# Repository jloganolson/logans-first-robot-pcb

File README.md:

# Logan's first robot PCB

A power distribution and USB board for a two-wheeled robot with a Jetson AGX
Thor, Dynamixel servos and two 8S battery packs. It is my first real board,
it was designed with heavy help from AI coding agents, and **it has not been
built yet**. I'm publishing it to get it reviewed before I spend money on it.

> **Status (10 November 2026): not ordered.** The current revision is
> **v0.11**: 228 × 155 mm, every plug on a board edge, fully labelled. An
> unpaid JLCPCB quote exists at $321.20 for five boards with two assembled,
> but it was made from a build in which a review found a copper fault (a
> 0.37 mm neck feeding the XL330 plugs). The files here hold the corrected
> build, which has not been uploaded, quoted or independently reviewed (see
> [Open questions](#open-questions)). Nothing here has been measured on hardware.

v0.10 had an empty quarter and plugs in the middle of the board. v0.11
re-floorplans the hobby-servo block and moves the plugs to the edges:

## What it does

| Function | Detail |
|---|---|
| Battery input | Two 8S packs (27–33.6 V), each fused at the pack, through an external mechanical DPST master switch |
| Motor output | Fused battery-voltage passthrough to existing motor controllers (about 10 A in my use) |
| Jetson Thor | 24.3 V at up to 8 A, LM5146 synchronous buck, Micro-Fit plug on the left edge |
| Servo rails | 5 V (XL330), 10.8 V (XL430) and a separate 5 V (three MG90S), each a TPS54560 buck |
| Spare outputs | 5 V / 5 A and 11.7 V / 5 A on XT30 connectors |
| Audio | CM108B USB codec and TPA3118 stereo amplifier |
| USB | One USB-C to the Jetson; CH334F hub to audio, a CH342F dual UART for Dynamixel, and an STM32F072 that generates three servo PWM signals |

Four layers, 228 × 155 mm, 1 oz outer / 0.5 oz inner copper. 366 footprints, of which 304 are fitted by the factory.

## Look at it without installing anything

- **[Plain-language walkthrough](https://jloganolson.github.io/logans-first-robot-pcb/)**: what plugs in where, what it costs, what the risks are
- **[Schematic (PDF)](renders/schematic.pdf)**. See the caveat about its style below.
- [Silkscreen labels and pads](renders/board-labels.png)
- Copper layers: [top](renders/top-copper.png), [inner 1, ground](renders/inner1-ground.png), [inner 2, power](renders/inner2-power.png), [bottom](renders/bottom-copper.png), and the [assembly drawing](renders/assembly-top.png)
- Open the real board in your browser with KiCanvas: [board](https://kicanvas.org/?github=https://github.com/jloganolson/logans-first-robot-pcb/blob/main/revisions/v0.11/kicad/robot_pdb.kicad_pcb), [schematic](https://kicanvas.org/?github=https://github.com/jloganolson/logans-first-robot-pcb/blob/main/revisions/v0.11/kicad/robot_pdb.kicad_sch). The board file is about 6 MB, so it may be slow.
- KiCad 7 project: [`revisions/v0.11/kicad/`](revisions/v0.11/kicad/)

## Open questions

These are what I most want a second opinion on. Short answers are welcome;
"that's fine, everyone does it" is as useful to me as "don't".

1. **Inductor voltage ratings.** A reviewer pointed out that the molded
   inductors first chosen (Sunlord MWSA1004S, and a Cjiang part on the Thor
   rail) are rated 30 V across the winding while the packs reach 33.6 V. At
   start-up, or into a shorted output, the full input voltage sits across a
   buck inductor for each on-time. v0.11 therefore uses a 60 V Coilcraft
   XAL1510-103 on the Thor rail and 75 V Vishay IHLP-4040DZ-01 parts on the
   six TPS54560 rails, on the existing pads (about $30 in total). Was that
   necessary, or does the rating only matter in steady state? Is fitting an
   IHLP-4040 on a land pattern drawn for the Sunlord part acceptable
   (Vishay's recommended land lies inside the existing pads)?
2. **Thor buck current limit.** LM5146 with low-side RDS(on) sensing,
   R13 = 220 Ω, BSC034N06NS FETs. I calculate a typical valley limit near
   14 A (scaled from about 12 A at the earlier 180 Ω), a worst-case low near 8.5 A of load, and a worst-case inductor peak
   near 26 A (that figure was worked out against the v0.10 inductor's 29 A typical saturation; v0.11's Coilcraft XAL1510-103 is the part the design originally used). Two reviewers read the
   comparator offset's sign differently. See the [review handoff](docs/HANDOFF_V10_VALUE_ENGINEERED.md).
3. **USB 2.0 High-Speed pair.** 0.275 mm traces with a 0.19 mm gap over
   0.21 mm of 7628 prepreg (JLCPCB's calculator gives 90 Ω at 0.269 / 0.175).
   No impedance test coupon. Two older Full-Speed routes have
   [known reference-plane compromises](docs/V09_USB_PROTOTYPE_REVIEW.md).
4. **Heat.** A simple model from the real copper puts the hottest regulator
   about 45 °C above ambient at typical loads in still air, and about 78 °C
   with every output at its rated current ([map](renders/thermal-map.png),
   [model](red-team-findings/2026-11-10/thermal/)). Sensible for a board that
   will sit in a vented enclosure, or a sign the 1 oz / 0.5 oz copper is too thin?
5. **Assembly process.** JLCPCB's Economic line reflows at a fixed
   255 ± 5 °C. A reviewer reports a 250 °C case limit for the nine 10 × 10 mm
   electrolytic capacitors. Also: lead-free HASL under a 1.5 × 2 mm UQFN-10.
6. **The v0.11 changes.** The bottom strip (servo 5 V buck in the
   bottom-left corner, its fuse, the output buffer, the STM32) was re-placed
   by script, and fifteen signal links were auto-routed. The Thor plug moved
   to the left edge on a new 45 mm copper strip (In2 and bottom layer in
   parallel, about 2 mΩ by hand estimate), and the four Dynamixel plugs moved
   to the bottom edge (10.8 V on about 78 mm of In2, about 6.5 mΩ). It passes
   DRC, but nobody has reviewed the final build. Details in the
   [v0.11 handoff](docs/HANDOFF_V11_COMPACT_LAYOUT.md).
7. **Anything alarming** in the input protection (ideal-diode controller,
   TVS, fusing) or anywhere else.

## How to give feedback

Open an [issue](https://github.com/jloganolson/logans-first-robot-pcb/issues).
One issue per concern is easiest. Screenshots and "look at this net" pointers
are plenty; you don't need to propose a fix.

## How this was made, and what that means for you

- **AI-assisted and script-generated.** The schematic and layout were produced
  by Python scripts driving KiCad, written by AI agents under my direction.
  The scripts are in [`source/`](source/). Many of the older ones refer to
  earlier revisions that are not in this repository and will not run as-is.
- **The schematic is not a conventional drawing.** It is generated from a
  parts list: components are grouped by function and connected by net labels,
  with no drawn wires. It is electrically complete and matches the board, but
  it is harder to read than a hand-drawn schematic. Sorry.
- **v0.10 is a cost-reduced copy of v0.9.** A script
  ([`build_v10.py`](source/generator/build_v10.py)) takes the earlier, more
  expensive v0.9 board and applies a fixed list of changes: thinner copper,
  a shorter outline, standard via sizes, wider USB traces for the standard
  stack-up, and four part substitutions. Every change is recorded in
  [`derivation.json`](revisions/v0.10/derivation.json).
- **v0.11 is v0.10 with one area laid out again.** A second script
  ([`build_v11.py`](source/generator/build_v11.py)) moves each sub-circuit of
  the hobby-servo block as a rigid piece with its own copper, rebuilds the
  connections between them (planes for power, a grid maze router for
  signals), moves the Thor and Dynamixel plugs to the board edges, re-labels
  the silkscreen ([`labels_v11.py`](source/generator/labels_v11.py)) and
  trims the outline. The regulators, USB and audio circuitry did not move. Record: [`derivation.json`](revisions/v0.11/derivation.json).

## What has been checked

- KiCad DRC on v0.11: 0 errors, 0 unconnected pads, 11 warnings (dangling
  track ends and two library mismatches, all inherited).
- A [difference audit](source/fabrication/audit_v10.py) proving v0.10 differs
  from v0.9 only in the recorded ways, and a [second one](source/fabrication/audit_v11.py)
  proving v0.11 differs from v0.10 only in the servo block, the recorded plug
  moves and their new copper, with no part or net changed, and that schematic
  and board agree.
- JLCPCB accepted the v0.11 files, matched all 81 BOM lines and priced the order.
- **Every oriented part was checked one at a time in JLCPCB's placement
  viewer.** Thirteen were rotated wrongly in the placement file (including
  all six TPS54560s and the LM5146) and were corrected. The v0.9 and v0.10
  placement files in this repository still contain those errors.
- Three AI reviews of v0.10 and one of an early v0.11. Their reports, and
  [which of their findings held up](red-team-findings/2026-11-10/argon/DISPOSITION_v11.md),
  are in [`red-team-findings/`](red-team-findings/2026-11-10/).
  **None of them has seen the final v0.11.**

Not done: no board has been built, powered or measured. The thermal and
impedance figures are calculations.

## Ordering it from JLCPCB

Everything specific to JLCPCB is in [`manufacturing/jlcpcb/`](manufacturing/jlcpcb/):
Gerbers, BOM with their part numbers, placement file, the dated quote, and an
[order recipe](manufacturing/jlcpcb/ORDER_RECIPE.md) listing every option and
the mistakes that cost time to find. **Please don't order it as-is** while the
questions above are open.

## Repository map

| Path | Contents |
|---|---|
| `revisions/v0.11/` | The current board: KiCad project, change record, DRC report |
| `revisions/v0.10/`, `revisions/v0.9/` | The earlier boards it is derived from |
| `renders/` | Schematic PDF, layer images, thermal map |
| `manufacturing/jlcpcb/` | Order files and recipe |
| `docs/` | Walkthrough, review handoff, bring-up checklist, design notes |
| `red-team-findings/` | Cost review, AI review reports, thermal model |
| `source/` | Generator, audit and export scripts |
| `outputs/` | Audit results and the exact uploaded package |
| `firmware/robot_io/` | Firmware for the servo PWM controller (third-party USB stack not included; see its README) |

## License

MIT; see [LICENSE](LICENSE). Footprints and symbols taken from the KiCad
libraries remain under their own license (CC BY-SA 4.0 with the KiCad
library exception). This is an unbuilt prototype with known open issues and
comes with no warranty of any kind. It handles battery power: if you build
anything from it, fuse it and test it carefully.

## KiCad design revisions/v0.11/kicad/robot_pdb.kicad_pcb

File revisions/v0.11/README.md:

# Compact, edge-connector prototype v0.11

v0.10 with the hobby-servo block laid out again (228 x 155 mm instead of
228 x 195 mm), every plug moved to a board edge, a full set of silkscreen
labels, the Thor inductor (L1) back to the 60 V Coilcraft XAL1510-103MED, and
the six TPS54560 regulator inductors changed to 75 V Vishay IHLP-4040DZ-01.
Same circuit and parts list otherwise.

- Start here as the owner: [walkthrough](../../docs/PROTOTYPE_v0.11_WALKTHROUGH.html)
- Start here as a reviewer: [handoff](../../docs/HANDOFF_V11_COMPACT_LAYOUT.md)
- Every change, machine-readable: [derivation.json](derivation.json)

Board SHA-256 `494e931955b16b8dfd104733f677654027731623739dc754a6e77bf2939baaf2`.
This build fixes a 0.37 mm neck in the XL330 5 V copper that a fabrication
review found in build `9e2ac58e2b29`. The unpaid cart entry
`Robot_PDB_v11_Gerbers_Y8` ($321.20) still holds that earlier build and must
not be ordered; the corrected package has not been uploaded. No purchase made;
no hardware built or measured; the fix has not been independently reviewed.

```sh
export PDB_KICAD_STATE=/tmp/pdb-kicad-red-team
bash source/fabrication/with_kicad.sh /usr/bin/python3 source/generator/build_v11.py
bash source/fabrication/with_kicad.sh /usr/bin/python3 source/fabrication/audit_v11.py
bash source/fabrication/with_kicad.sh /usr/bin/python3 source/fabrication/export_v11.py
```

Rebuilding can change the board hash (zone refill), which invalidates the
uploaded package and the cart entry.

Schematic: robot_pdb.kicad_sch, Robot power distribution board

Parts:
C1, C5, C15, C103, C203, C303, C403, C503, C7103: 100nF 100V; C_0603_1608Metric; MPN MLCC X7R 100nF 100V; LCSC C15725
C2, C22, C61, C64, C71, C72, C86, C87, C95, C96, C98, C99, C104, C204, C304, C404, C504, C7023, C7024, C7025, C7026, C7028, C7043, C7104, C9900, C9905, C9906, C9908: 100nF 50V; C_0603_1608Metric; MPN MLCC X7R 100nF 50V; LCSC C14663
C3, C4, C14, C7111: 100uF 63V; CP_Elec_10x10; MPN Lelon VE-101M1JTR-1010 100uF 63V 10x10mm; LCSC C249468
C10, C11, C12, C13, C101, C102, C201, C202, C301, C302, C401, C402, C501, C502, C7101, C7102: 2.2uF 100V; C_1210_3225Metric; MPN MLCC X7R 2.2uF 100V; LCSC C55151
C16, C17, C18, C19, C84, C85: 10uF 50V; C_1210_3225Metric; MPN MLCC X7R 10uF 50V; LCSC C138687
C20: 220uF 35V; CP_Elec_10x10; MPN Lelon VUX221M1VTR-1010 220uF 35V 10x10mm; LCSC C3029711
C21, C73, C74, C75, C76, C77, C7022: 4.7uF 16V; C_0603_1608Metric; MPN MLCC X5R 4.7uF 16V; LCSC C19666
C23: 47nF; C_0603_1608Metric; MPN MLCC X7R 47nF; LCSC C1622
C24, C26: 2.2nF; C_0603_1608Metric; MPN MLCC X7R 2.2nF; LCSC C1604
C25, C110, C210, C310, C410, C510, C7110: 47pF; C_0603_1608Metric; MPN MLCC X7R 47pF; LCSC C1671
C27: 33pF 50V; C_0603_1608Metric; MPN MLCC C0G 33pF 50V; LCSC C1663
C60, C63, C70, C9901: 10uF 25V; C_0805_2012Metric; MPN MLCC X7R 10uF 25V; LCSC C15850
C62, C65, C66, C78, C79, C80, C81, C82, C83, C97, C7021, C7027, C9907: 1uF 25V; C_0603_1608Metric; MPN MLCC X7R 1uF 25V; LCSC C15849
C67: 100nF 50V; C_0603_1608Metric; MPN Yageo CC0603KRX7R9BB104; LCSC C14663
C88, C311, C411: 470uF 25V; CP_Elec_10x10; MPN Lelon VZH471M1ETR-1010 470uF 25V 10x10m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; LCSC C249933
C89, C90, C91, C92: 220nF 25V; C_0603_1608Metric; MPN MLCC X7R 220nF 25V; LCSC C21120
C93, C94: 680nF 50V; C_1206_3216Metric; MPN MLCC X7R 680nF 50V; LCSC C1881
C105, C106, C107, C108, C205, C206, C207, C208, C305, C306, C307, C308, C405, C406, C407, C408, C505, C506, C507, C508, C7105, C7106, C7107, C7108: 22uF 25V; C_0805_2012Metric; MPN MLCC X5R 22uF 25V; LCSC C45783
C109, C209, C309, C409, C509, C7109: 4.7nF; C_0603_1608Metric; MPN MLCC X7R 4.7nF; LCSC C53987
C7029, C7030: 18pF 50V; C_0603_1608Metric; MPN Samsung CL10C180JB8NNNC C0G5%; LCSC C1647
C7112: 470uF 25V; CP_Elec_10x10; MPN Lelon VZH471M1ETR-1010; LCSC C249933
C9902: 150uF 10V POSCAP; Panasonic_POSCAP_D3L; MPN Panasonic 10TPF150ML; LCSC C347559
C9909: 1nF 50V; C_0603_1608Metric; MPN Samsung CL10B102KB8NNNC; LCSC C1588
D1: SMCJ36CA; D_SMC; MPN Littelfuse SMCJ36CA bidirectional 36V T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; LCSC C151283
D2, D3, D60, D102, D202, D302, D402, D502, D7102: Green; LED_0603_1608Metric; MPN KT-0603G 0603 green LED; LCSC C12624
D101, D201, D301, D401, D501, D7101: SS1060; D_SMC; MPN SS1060 60V 10A SMC; LCSC C2922189
D7001: SMCJ36CA; D_SMC; MPN Littelfuse SMCJ36CA; LCSC C151283
F1: MOTOR 30A 500VDC; Fuse_505_Axial_P40mm; MPN Littelfuse 0505030.MXEP 30A 500VDC 20kA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; LCSC C187656
F2: ELECTRONICS 30A 500VDC; Fuse_505_Axial_P40mm; MPN Littelfuse 0505030.MXEP 30A 500VDC 20kA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; LCSC C187656
F7000: 5A63VDC20kA; Fuse_Schurter_SHF_6.3x32_P40mm; MPN SCHURTER8020.5075.PT
FB1: 120R 2A; L_0603_1608Metric; MPN Murata BLM18PG121SN1D; LCSC C14709
FB2: 600R; L_0603_1608Metric; MPN Sunlord GZ1608D601TF; LCSC C1002
H1, H2, H3, H4, H5, H6, H7: M3; MountingHole_3.2mm_M3
H7001, H7002, H7003, H7004: M3 NPTH; MountingHole_3.2mm_M3; MPN M3 NPTH
H9910, H9911, H9912: M3 NYLON SUPPORT; MountingHole_3.2mm_M3; MPN M3 nylon/insulating standoff
J1: PACK A (XT60 male); Power_WirePort_P7.2mm; MPN Hand-soldered 12AWG power pigtail; exte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
J2: FUSED BATTERY MOTOR PASSTHROUGH; Power_WirePort_P7.2mm; MPN Hand-soldered 12AWG power pigtail; exte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
J3: THOR 24V MICRO-FIT; MicroFit_43045_0412_4P_2oz; MPN Molex430450412; LCSC C277721
J4: PACK B (XT60 male); Power_WirePort_P7.2mm; MPN Hand-soldered 12AWG power pigtail; exte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
J5: EXTERNAL DPST POWER WIRES; Disconnect_WirePort_4Circuit; MPN Four hand-soldered 12AWG wires to exter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
J10: USB-C to Jetson; USB_C_HRO_31M12_2oz; MPN HRO TYPE-C-31-M-12 USB-C receptacle; LCSC C165948
J13: SPEAKER L (screw terminal); TerminalBlock_bornier-2_P5.08mm; MPN Kefa KF301-5.0-2P; LCSC C474881
J14: SPEAKER R (screw terminal); TerminalBlock_bornier-2_P5.08mm; MPN Kefa KF301-5.0-2P; LCSC C474881
J101: RASPBERRY PI 5V (XT30 female); AMASS_XT30PW_F_2oz; MPN Amass XT30PW-F; LCSC C2913282
J301: XL330 5V CHAIN A; JST_VH_B3P-VH_1x03_P3.96mm_Vertical; MPN JST B3P-VH(LF)(SN), use VHR-3N mating h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; LCSC C160316
J302: XL330 5V CHAIN B; JST_VH_B3P-VH_1x03_P3.96mm_Vertical; MPN JST B3P-VH(LF)(SN), use VHR-3N mating h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; LCSC C160316
J401: XL430 10.8V CHAIN; JST_VH_B3P-VH_1x03_P3.96mm_Vertical; MPN JST B3P-VH(LF)(SN), use VHR-3N mating h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; LCSC C160316
J402: XL430 10.8V CHAIN B; JST_VH_B3P-VH_1x03_P3.96mm_Vertical; MPN JST B3P-VH(LF)(SN), use VHR-3N mating h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; LCSC C160316
J501: 12V AUX (amp is on board) (XT30 female); AMASS_XT30PW_F_2oz; MPN Amass XT30PW-F; LCSC C2913282
J7004: MG90S1:GND/+5V/PWM; PinHeader_1x03_P2.54mm_Vertical; MPN hand-fit three-pin servo header; center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
J7005: MG90S2:GND/+5V/PWM; PinHeader_1x03_P2.54mm_Vertical; MPN hand-fit three-pin servo header; center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
J7006: MG90S3:GND/+5V/PWM; PinHeader_1x03_P2.54mm_Vertical; MPN hand-fit three-pin servo header; center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
J7008: PWM SWD:VREF/GND/DIO/CLK/RESET; PinHeader_1x05_P2.54mm_Vertical; MPN hand-fit SWD service header; pin1 is ta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
J9921: THOR OFF SHUNT; PinHeader_1x02_P2.54mm_Vertical; MPN Optional hand-fit 2.54mm two-pin header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
J9922: PI OFF SHUNT; PinHeader_1x02_P2.54mm_Vertical; MPN Optional hand-fit 2.54mm two-pin header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
J9923: USB CONTROL OFF SHUNT; PinHeader_1x02_P2.54mm_Vertical; MPN Optional hand-fit 2.54mm two-pin header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
J9924: XL330 OFF SHUNT; PinHeader_1x02_P2.54mm_Vertical; MPN Optional hand-fit 2.54mm two-pin header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
J9925: XL430 OFF SHUNT; PinHeader_1x02_P2.54mm_Vertical; MPN Optional hand-fit 2.54mm two-pin header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
J9926: AUDIO AUX OFF SHUNT; PinHeader_1x02_P2.54mm_Vertical; MPN Optional hand-fit 2.54mm two-pin header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
J9928: MG90S OFF SHUNT; PinHeader_1x02_P2.54mm_Vertical; MPN Optional hand-fit 2.54mm two-pin header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
JP1: 24V OFF; SolderJumper-2_P1.3mm_Open_RoundedPad1.0x1.5mm; MPN solder jumper (open, bridge with solder)
JP101, JP201, JP301, JP401, JP501, JP7101: OFF; SolderJumper-2_P1.3mm_Open_RoundedPad1.0x1.5mm; MPN solder jumper (open, bridge with solder)
JP7003: PWM DFU BOOT (OPEN); SolderJumper-2_P1.3mm_Open_RoundedPad1.0x1.5mm; MPN solder jumper (open, bridge with solder)
JP7005: PWM RESET (OPEN); SolderJumper-2_P1.3mm_Open_RoundedPad1.0x1.5mm; MPN solder jumper (open, bridge with solder)
L1: 10uH 22A 60V; L_Coilcraft_XAL1510-103; MPN Coilcraft XAL1510-103MED; LCSC C3911782
L2, L3, L4, L7002: 6.8uH 75V; L_Sunlord_MWSA1004S; MPN Vishay IHLP4040DZER6R8M01 (75V, Isat 13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; LCSC C845080
L5, L6: 10uH 75V; L_Sunlord_MWSA1004S; MPN Vishay IHLP4040DZER100M01 (75V, Isat 12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; LCSC C845065
L70, L71, L72, L73: 10uH; L_Sunlord_MWSA1004S; MPN Sunlord MWSA1004S-100MT (same part as t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; LCSC C408487
Q1: BSC040N10NS5; TDSON-8-1; MPN Infineon BSC040N10NS5ATMA1 100V 4mR at 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; LCSC C534334
Q2: BSC034N06NS; TDSON-8-1; MPN Infineon BSC034N06NS (high side); LCSC C534325
Q3: BSC034N06NS; TDSON-8-1; MPN Infineon BSC034N06NS (low side); LCSC C534325
Q7001: MMBT3904; SOT-23; MPN JSCJ MMBT3904(RANGE:100-300); LCSC C20526
R1, R19: 22k; R_0603_1608Metric; MPN 0603 1% 22k; LCSC C31850
R10, R16: 49.9k; R_0603_1608Metric; MPN 0603 1% 49.9k; LCSC C23184
R11, R103, R104, R203, R204, R303, R304, R403, R404, R503, R504, R7103, R7104: 220k; R_0603_1608Metric; MPN 0603 1% 220k; LCSC C22961
R12, R105, R106, R205, R206, R305, R306, R405, R505, R7105, R7106: 12k; R_0603_1608Metric; MPN 0603 1% 12k; LCSC C22790
R13: 220; R_0603_1608Metric; MPN 0603 1% 220; LCSC C22962
R14: 150k; R_0603_1608Metric; MPN 0603 1% 150k; LCSC C22807
R15, R60, R61: 5.1k; R_0603_1608Metric; MPN 0603 1% 5.1k; LCSC C23186
R17, R63: 1k; R_0603_1608Metric; MPN 0603 1% 1k; LCSC C21190
R62, R70, R76, R77, R407, R507, R7022, R7023, R7047, R7051, R7052, R7053: 10k; R_0603_1608Metric; MPN 0603 1% 10k; LCSC C25804
R71, R72, R7048, R7049, R7057, R7058, R7059, R9900, R9904: 100k; R_0603_1608Metric; MPN 0603 1% 100k; LCSC C25803
R73: 5.6k; R_0603_1608Metric; MPN 0603 1% 5.6k; LCSC C23189
R74, R75: 4.7k; R_0603_1608Metric; MPN 0603 1% 4.7k; LCSC C23162
R101, R201, R301, R7101: 39k; R_0603_1608Metric; MPN 0603 1% 39k; LCSC C23153
R102, R202, R302, R7102, R9902: 7.5k; R_0603_1608Metric; MPN 0603 1% 7.5k; LCSC C23234
R107, R207, R307, R502, R7046, R7107: 2.2k; R_0603_1608Metric; MPN 0603 1% 2.2k; LCSC C4190
R401, R501, R9901: 30k; R_0603_1608Metric; MPN 0603 1% 30k; LCSC C22984
R402: 2.4k; R_0603_1608Metric; MPN 0603 1% 2.4k; LCSC C22940
R406, R506, R9908: 20k; R_0603_1608Metric; MPN 0603 1% 20k; LCSC C4184
R7021: 10; R_0603_1608Metric; MPN UNI-ROYAL 0603WAF100JT5E; LCSC C22859
R7054, R7055, R7056: 100; R_0603_1608Metric; MPN UNI-ROYAL 0603WAF1000T5E; LCSC C22775
R7108: 300; R_0603_1608Metric; MPN 0603 1% 300; LCSC C23025
R9903: 10k; R_0603_1608Metric; MPN UNI-ROYAL 0603WAF1002T5E; LCSC C25804
R9906, R9907: 49.9; R_0603_1608Metric; MPN UNI-ROYAL 0603WAF499JT5E; LCSC C23185
R9909: 220k; R_0603_1608Metric; MPN UNI-ROYAL 0603WAF2203T5E; LCSC C22961
R9910: 100k; R_0603_1608Metric; MPN UNI-ROYAL 0603WAF1003T5E; LCSC C25803
TP1: VIN; TestPoint_Pad_D1.5mm; MPN bare copper test pad
TP2, TP7004: GND; TestPoint_Pad_D1.5mm; MPN bare copper test pad
TP3: SW24; TestPoint_Pad_D1.5mm; MPN bare copper test pad
TP4: 24V; TestPoint_Pad_D1.5mm; MPN bare copper test pad
TP5: PG24; TestPoint_Pad_D1.5mm; MPN bare copper test pad
TP101: 5V_PI; TestPoint_Pad_D1.5mm; MPN bare copper test pad
TP102, TP202, TP302, TP402, TP502, TP7102: SW; TestPoint_Pad_D1.5mm; MPN bare copper test pad
TP201: USB CONTROL 5V; TestPoint_Pad_D1.5mm; MPN bare copper test pad
TP301: 5V_SRV; TestPoint_Pad_D1.5mm; MPN bare copper test pad
TP401: 12V_SRV; TestPoint_Pad_D1.5mm; MPN bare copper test pad
TP501: 12V_AUD; TestPoint_Pad_D1.5mm; MPN bare copper test pad
TP7002: PWM3V3; TestPoint_Pad_D1.5mm; MPN bare copper test pad
TP7003: PWM OE_N; TestPoint_Pad_D1.5mm; MPN bare copper test pad
TP7101: V5_SERVO; TestPoint_Pad_D1.5mm; MPN bare copper test pad
U1: LM74700QDBVRQ1; SOT-23-6; MPN TI LM74700-Q1 ideal diode controller; LCSC C2941042
U2: LM5146RGYR; Texas_RGY_R-PVQFN-N20_EP2.05x3.05mm; MPN Texas Instruments LM5146RGYR; LCSC C3188679
U3, U4, U5, U6, U7, U7003: TPS54560DDAR; TI_SO-PowerPAD-8_ThermalVias; MPN TI TPS54560 60V 5A buck; LCSC C31966
U10: CH334F; QFN-24-1EP_4x4mm_P0.5mm_EP2.6x2.6mm; MPN WCH CH334F USB 2.0 4-port hub (MTT); LCSC C5187527
U11: USBLC6-2SC6; SOT-23-6; MPN ST USBLC6-2SC6 USB ESD; LCSC C7519
U12: CM108B; LQFP-48_7x7mm_P0.5mm; MPN C-Media CM108B USB audio codec (crystal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; LCSC C371347
U13: TPA3118D2DAPR; HTSSOP-32-1EP_6.1x11mm_P0.65mm_EP5.2x11mm_Mask4.11x4.36mm_T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; MPN TI TPA3118D2 2x30W class-D, pad down; LCSC C46497
U14: CH342F; QFN-24-1EP_4x4mm_P0.5mm_EP2.6x2.6mm; MPN WCH CH342F USB to dual UART (half-duple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; LCSC C2841530
U15, U16: SN74LVC2G241DCUR; VSSOP-8_2.3x2mm_P0.5mm; MPN TI SN74LVC2G241 (RX buffer /OE, TX buff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; LCSC C10430
U17: AP2112K-3.3TRG1; SOT-23-5; MPN Diodes AP2112K-3.3TRG1, dedicated 3.3V 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; LCSC C51118
U7002: STM32F072CBT6; LQFP-48_7x7mm_P0.5mm; MPN ST STM32F072CBT6 128KB flash; LCSC C81720
U7006: AP2112K-3.3TRG1; SOT-23-5; MPN Diodes AP2112K-3.3TRG1; LCSC C51118
U7007: SN74AHCT125QPWRQ1; TSSOP-14_4.4x5mm_P0.65mm; MPN Texas Instruments SN74AHCT125QPWRQ1; LCSC C507215
U7009: USBLC6-2SC6; SOT-23-6; MPN ST USBLC6-2SC6; LCSC C7519
U9900: TPS2552DBVR; SOT-23-6; MPN Texas Instruments TPS2552DBVR; LCSC C46506
U9902: TS3USB221ARSER; Texas_UQFN-10_1.5x2mm_P0.5mm; MPN Texas Instruments TS3USB221ARSER; LCSC C128396
U9903: TLV3011BIDBVR MANUAL FIT; SOT-23-6; MPN Texas Instruments TLV3011BIDBVR; LCSC C20345920
U9904: TPS2553DBVR; SOT-23-6; MPN Texas Instruments TPS2553DBVR; LCSC C55266
Y1: 12MHz; Crystal_SMD_3225-4Pin_3.2x2.5mm; MPN 12MHz 3225 crystal (CH334F has internal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; LCSC C9002
Y7002: 8MHz CL12pF; Crystal_SMD_3225-4Pin_3.2x2.5mm; MPN YXC X32258MOB4SI; LCSC C2682775

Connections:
+5V_PI: C105.1, C106.1, C107.1, C108.1, J101.2, L2.2, R101.1, R107.1, TP101.1
+5V_SRV: C305.1, C306.1, C307.1, C308.1, C311.1, J301.2, J302.2, L4.2, R301.1, R307.1, TP301.1
+12V_AUD: C83.1, C84.1, C85.1, C86.1, C87.1, C88.1, C505.1, C506.1, C507.1, C508.1, J501.2, L6.2, R71.1, R501.1, R507.1, TP501.1, U13.17 (AVCC), U13.18 (PVCC), U13.19 (PVCC), U13.31 (PVCC), U13.32 (PVCC)
+12V_SRV: C405.1, C406.1, C407.1, C408.1, C411.1, J401.2, J402.2, L5.2, R401.1, R407.1, TP401.1
+24V: C16.1, C17.1, C18.1, C19.1, C20.1, J3.1, J3.2, L1.2, R14.1, R17.1, R19.1, TP4.1
AMP_BSNL: C89.1, U13.20 (BSNL)
AMP_BSNR: C91.1, U13.26 (BSNR)
AMP_BSPL: C90.1, U13.24 (BSPL)
AMP_BSPR: C92.1, U13.30 (BSPR)
AMP_GAIN: R73.1, U13.8 (GAIN/SLV)
AMP_GVDD: C82.1, U13.6 (PLIMIT), U13.7 (GVDD)
AMP_LINN: C79.2, U13.11 (LINN)
AMP_LINP: C78.2, U13.10 (LINP)
AMP_MUTE: R72.1, U13.12 (MUTE)
AMP_OUTNL: C89.2, L73.1, U13.21 (OUTNL)
AMP_OUTNR: C91.2, L71.1, U13.27 (OUTNR)
AMP_OUTPL: C90.2, L72.1, U13.23 (OUTPL)
AMP_OUTPR: C92.2, L70.1, U13.29 (OUTPR)
AMP_RINN: C81.2, U13.5 (RINN)
AMP_RINP: C80.2, U13.4 (RINP)
AMP_SDZ: R71.2, U13.2 (SDZ), U13.3 (FAULTZ)
AUD_LOBS: C77.1, C79.1, C81.1, U12.31 (LOBS)
AUD_LOL: C78.1, U12.30 (LOL)
AUD_LOR: C80.1, U12.32 (LOR)
A_AVDD: C70.1, C71.1, FB2.2, U12.29 (AVDD), U12.34 (AVDD)
A_BST: C504.1, U7.1 (BOOT)
A_COMP: C510.1, R506.1, U7.6 (COMP)
A_CZ: C509.1, R506.2
A_EN: J9926.1, JP501.1 (A), R504.2, R505.1, U7.3 (EN)
A_FB: R501.2, R502.1, U7.5 (FB)
A_MODE: R70.2, U12.10 (MODE)
A_REG18: C73.1, U12.8 (DREG18)
A_REG33: C74.1, U12.9 (DREG33)
A_REG36: C75.1, U12.37 (AREG36)
A_RT: R503.1, U7.4 (RT/CLK)
A_SW: C504.2, D501.1 (K), L6.1, TP502.1, U7.8 (SW)
A_VREF: C76.1, U12.26 (VREF)
D2_A: D2.2 (A), R1.2
D3_A: D3.2 (A), R19.2
D60_A: D60.2 (A), R63.2
D102_A: D102.2 (A), R107.2
D202_A: D202.2 (A), R207.2
D302_A: D302.2 (A), R307.2
D402_A: D402.2 (A), R407.2
D502_A: D502.2 (A), R507.2
DXL0_RX: U14.20 (RXD0), U15.6 (1Y)
DXL0_TNOW: R74.1, U14.23 (DTR0/TNOW0), U15.1 (1OE#), U15.7 (2OE)
DXL0_TX: U14.21 (TXD0), U15.5 (2A)
DXL1_RX: U14.12 (RXD1), U16.6 (1Y)
DXL1_TNOW: R75.1, U14.15 (DTR1/TNOW1), U16.1 (1OE#), U16.7 (2OE)
DXL1_TX: U14.13 (TXD1), U16.5 (2A)
DXL330_DATA: J301.3, J302.3, R76.2, U15.2 (1A), U15.3 (2Y)
DXL430_DATA: J401.3, J402.3, R77.2, U16.2 (1A), U16.3 (2Y)
GND: C1.2, C3.2, C4.2, C5.2, C10.2, C11.2, C12.2, C13.2, C14.2, C15.2, C16.2, C17.2, C18.2, C19.2, C20.2, C21.2, C23.2, C27.2, C60.2, C61.2, C62.2, C63.2, C64.2, C65.2, C66.2, C67.2, C70.2, C71.2, C72.2, C73.2, C74.2, C75.2, C76.2, C77.2, C82.2, C83.2, C84.2, C85.2, C86.2, C87.2, C88.2, C95.2, C96.2, C97.2, C98.2, C99.2, C101.2, C102.2, C103.2, C105.2, C106.2, C107.2, C108.2, C109.2, C110.2, C201.2, C202.2, C203.2, C205.2, C206.2, C207.2, C208.2, C209.2, C210.2, C301.2, C302.2, C303.2, C305.2, C306.2, C307.2, C308.2, C309.2, C310.2, C311.2, C401.2, C402.2, C403.2, C405.2, C406.2, C407.2, C408.2, C409.2, C410.2, C411.2, C501.2, C502.2, C503.2, C505.2, C506.2, C507.2, C508.2, C509.2, C510.2, C7021.2, C7022.2, C7023.2, C7024.2, C7025.2, C7026.2, C7027.2, C7028.2, C7029.2, C7030.2, C7043.2, C7101.2, C7102.2, C7103.2, C7105.2, C7106.2, C7107.2, C7108.2, C7109.2, C7110.2, C7111.2, C7112.2, C9900.2, C9901.2, C9902.2, C9905.2, C9906.2, C9907.2, C9908.2, C9909.2, D1.2 (A2), D2.1 (K), D3.1 (K), D101.2 (A), D102.1 (K), D201.2 (A), D202.1 (K), D301.2 (A), D302.1 (K), D401.2 (A), D402.1 (K), D501.2 (A), D502.1 (K), D7001.2 (A2), D7101.2 (A), D7102.1 (K), J1.1, J2.1, J3.3, J3.4, J4.1, J10.A1 (GND), J10.A12 (GND), J10.B1 (GND), J10.B12 (GND), J10.S1 (SHIELD), J101.1, J301.1, J302.1, J401.1, J402.1, J501.1, J7004.1, J7005.1, J7006.1, J7008.2, J9921.2, J9922.2, J9923.2, J9924.2, J9925.2, J9926.2, J9928.2, JP1.2 (B), JP101.2 (B), JP201.2 (B), JP301.2 (B), JP401.2 (B), JP501.2 (B), JP7005.2 (B), JP7101.2 (B), Q3.1 (S), Q3.2 (S), Q3.3 (S), Q7001.2 (E), R10.2, R12.2, R15.2, R60.2, R61.2, R70.1, R72.2, R73.2, R74.2, R75.2, R102.2, R103.2, R105.2, R202.2, R203.2, R205.2, R302.2, R303.2, R305.2, R402.2, R403.2, R405.2, R502.2, R503.2, R505.2, R7023.2, R7048.2, R7049.2, R7051.2, R7052.2, R7053.2, R7057.2, R7058.2, R7059.2, R7102.2, R7103.2, R7105.2, R9902.2, R9903.2, R9906.2, R9907.2, R9908.2, R9910.2, TP2.1, TP7004.1, U1.2 (GND), U2.6 (AGND), U2.8 (SYNCIN), U2.12 (PGND), U2.15 (EP15), U2.21 (PAD), U3.7 (GND), U3.9 (PAD), U4.7 (GND), U4.9 (PAD), U5.7 (GND), U5.9 (PAD), U6.7 (GND), U6.9 (PAD), U7.7 (GND), U7.9 (PAD), U10.25 (GND), U11.2 (GND), U12.14 (DVSS), U12.23 (TEST), U12.24 (AVSS), U12.33 (AVSS), U12.36 (DVSS), U13.1 (MODSEL), U13.9 (GND), U13.13 (AM2), U13.14 (AM1), U13.15 (AM0), U13.22 (GND), U13.25 (GND), U13.28 (GND), U13.33 (PAD), U14.2 (GND), U14.25 (EP), U15.4 (GND), U16.4 (GND), U17.2 (GND), U7002.8 (VSSA), U7002.23 (VSS), U7002.35 (VSS), U7002.47 (VSS), U7003.7 (GND), U7003.9 (PAD), U7006.2 (GND), U7007.7 (GND), U7007.12 (4A), U7009.2 (GND), U9900.2 (GND), U9902.5 (GND), U9902.9 (S), U9903.2 (GND), U9904.2 (GND), Y1.2 (GND), Y1.4 (GND), Y7002.2 (GND), Y7002.4 (GND)
HUB_PSELF_NC: U10.18 (PSELF)
HUB_UP_DM: U10.14 (DMU), U9902.2 (1D-)
HUB_UP_DP: U10.15 (DPU), U9902.1 (1D+)
H_BST: C404.1, U6.1 (BOOT)
H_COMP: C410.1, R406.1, U6.6 (COMP)
H_CZ: C409.1, R406.2
H_EN: J9925.1, JP401.1 (A), R404.2, R405.1, U6.3 (EN)
H_FB: R401.2, R402.1, U6.5 (FB)
H_LED: D60.1 (K), U10.22 (LED1)
H_OVCUR: R62.2, U10.1 (OVCUR#), U9900.4 (FAULT_N)
H_PWREN_N: R9900.1, U10.24 (PWREN#), U9900.3 (EN_N)
H_RT: R403.1, U6.4 (RT/CLK)
H_SW: C404.2, D401.1 (K), L5.1, TP402.1, U6.8 (SW)
H_V33: C63.1, C64.1, C9905.1, C9906.1, R62.1, R63.1, R9900.2, R9904.2, U10.20 (VDD33), U9902.10 (VCC), U9903.6 (V+)
H_XI: U10.4 (XI), Y1.1 (X1)
H_XO: U10.3 (XO), Y1.3 (X2)
IO_D102_A: D7102.2 (A), R7107.2
IO_NC_PWM_2: U7002.2 (PC13)
IO_NC_PWM_3: U7002.3 (PC14)
IO_NC_PWM_4: U7002.4 (PC15)
IO_NC_PWM_10: U7002.10 (PA0)
IO_NC_PWM_11: U7002.11 (PA1)
IO_NC_PWM_12: U7002.12 (PA2)
IO_NC_PWM_13: U7002.13 (PA3)
IO_NC_PWM_14: U7002.14 (PA4)
IO_NC_PWM_15: U7002.15 (PA5)
IO_NC_PWM_20: U7002.20 (PB2)
IO_NC_PWM_21: U7002.21 (PB10)
IO_NC_PWM_22: U7002.22 (PB11)
IO_NC_PWM_25: U7002.25 (PB12)
IO_NC_PWM_26: U7002.26 (PB13)
IO_NC_PWM_27: U7002.27 (PB14)
IO_NC_PWM_28: U7002.28 (PB15)
IO_NC_PWM_29: U7002.29 (PA8)
IO_NC_PWM_30: U7002.30 (PA9)
IO_NC_PWM_31: U7002.31 (PA10)
IO_NC_PWM_38: U7002.38 (PA15)
IO_NC_PWM_39: U7002.39 (PB3)
IO_NC_PWM_40: U7002.40 (PB4)
IO_NC_PWM_41: U7002.41 (PB5)
IO_NC_PWM_42: U7002.42 (PB6)
IO_NC_PWM_43: U7002.43 (PB7)
IO_NC_PWM_45: U7002.45 (PB8_CAN_RX)
IO_NC_PWM_46: U7002.46 (PB9_CAN_TX)
IO_NC_PWM_BUFFER4: U7007.11 (4Y)
IO_PWM1_BUF: R7054.1, U7007.3 (1Y)
IO_PWM1_MCU: R7051.1, U7002.16 (PA6), U7007.2 (1A)
IO_PWM1_OUT: J7004.3, R7054.2, R7057.1
IO_PWM2_BUF: R7055.1, U7007.6 (2Y)
IO_PWM2_MCU: R7052.1, U7002.17 (PA7), U7007.5 (2A)
IO_PWM2_OUT: J7005.3, R7055.2, R7058.1
IO_PWM3_BUF: R7056.1, U7007.8 (3Y)
IO_PWM3_MCU: R7053.1, U7002.18 (PB0), U7007.9 (3A)
IO_PWM3_OUT: J7006.3, R7056.2, R7059.1
IO_PWM_BOOT0: JP7003.2 (B), R7023.1, U7002.44 (BOOT0)
IO_PWM_BST: C7104.1, U7003.1 (BOOT)
IO_PWM_COMP: C7110.1, R7106.1, U7003.6 (COMP)
IO_PWM_CZ: C7109.1, R7106.2
IO_PWM_EN: J9928.1, JP7101.1 (A), R7104.2, R7105.1, U7003.3 (EN)
IO_PWM_FB: R7102.1, R7108.2, U7003.5 (FB)
IO_PWM_FB_TOP: R7101.2, R7108.1
IO_PWM_HSE_IN: C7029.1, U7002.5 (PF0_OSC_IN), Y7002.1 (X1)
IO_PWM_HSE_OUT: C7030.1, U7002.6 (PF1_OSC_OUT), Y7002.3 (X2)
IO_PWM_NRST: C7028.1, J7008.5, JP7005.1 (A), R7022.2, U7002.7 (NRST)
IO_PWM_RT: R7103.1, U7003.4 (RT/CLK)
IO_PWM_SW: C7104.2, D7101.1 (K), L7002.1, TP7102.1, U7003.8 (SW)
IO_PWM_SWCLK: J7008.4, U7002.37 (PA14_SWCLK)
IO_PWM_SWDIO: J7008.3, U7002.34 (PA13_SWDIO)
IO_SERVO_ARM: R7047.1, R7049.1, U7002.19 (PB1)
IO_SERVO_OE_BASE: Q7001.1 (B), R7047.2, R7048.1
IO_SERVO_OE_N: Q7001.3 (C), R7046.2, TP7003.1, U7007.1 (1OE_N), U7007.4 (2OE_N), U7007.10 (3OE_N)
IO_V3_PWM: C7022.1, C7023.1, C7024.1, C7025.1, J7008.1, JP7003.1 (A), R7021.1, R7022.1, TP7002.1, U7002.1 (VBAT), U7002.24 (VDD), U7002.36 (VDDIO2), U7002.48 (VDD), U7006.5 (VOUT)
IO_V3_PWM_A: C7026.1, C7027.1, R7021.2, U7002.9 (VDDA)
NC_HUB_P3_DM: U10.7 (DM3)
NC_HUB_P3_DP: U10.8 (DP3)
O_BST: C204.1, U4.1 (BOOT)
O_COMP: C210.1, R206.1, U4.6 (COMP)
O_CZ: C209.1, R206.2
O_EN: J9923.1, JP201.1 (A), R204.2, R205.1, U4.3 (EN)
O_FB: R201.2, R202.1, U4.5 (FB)
O_RT: R203.1, U4.4 (RT/CLK)
O_SW: C204.2, D201.1 (K), L3.1, TP202.1, U4.8 (SW)
P1_DM: U10.11 (DM1), U12.42 (USBDM)
P1_DP: U10.12 (DP1), U12.41 (USBDP)
P2_DM: U10.9 (DM2), U14.4 (UD-)
P2_DP: U10.10 (DP2), U14.3 (UD+)
P4_DM: U10.5 (DM4), U7002.32 (PA11_USB_DM), U7009.3 (IO2), U7009.4 (IO2)
P4_DP: U10.6 (DP4), U7002.33 (PA12_USB_DP), U7009.1 (IO1), U7009.6 (IO1)
PACK_A_POS: J1.2, J5.1
PACK_B_POS: J4.2, J5.3
PWM_5V: C7043.1, C7105.1, C7106.1, C7107.1, C7108.1, C7112.1, J7004.2, J7005.2, J7006.2, L7002.2, R7046.1, R7101.1, R7107.1, TP7101.1, U7007.13 (4OE_N), U7007.14 (VCC)
PWM_VIN: C7101.1, C7102.1, C7103.1, C7111.1, D7001.1 (A1), F7000.2, R7104.1, U7003.2 (VIN)
P_BST: C104.1, U3.1 (BOOT)
P_COMP: C110.1, R106.1, U3.6 (COMP)
P_CZ: C109.1, R106.2
P_EN: J9922.1, JP101.1 (A), R104.2, R105.1, U3.3 (EN)
P_FB: R101.2, R102.1, U3.5 (FB)
P_RT: R103.1, U3.4 (RT/CLK)
P_SW: C104.2, D101.1 (K), L2.1, TP102.1, U3.8 (SW)
Q1_G: Q1.4 (G), U1.5 (GATE)
SPK_LN: C94.2, J13.1, L73.2
SPK_LP: C94.1, J13.2, L72.2
SPK_RN: C93.2, J14.1, L71.2
SPK_RP: C93.1, J14.2, L70.2
S_BST: C304.1, U5.1 (BOOT)
S_COMP: C310.1, R306.1, U5.6 (COMP)
S_CZ: C309.1, R306.2
S_EN: J9924.1, JP301.1 (A), R304.2, R305.1, U5.3 (EN)
S_FB: R301.2, R302.1, U5.5 (FB)
S_RT: R303.1, U5.4 (RT/CLK)
S_SW: C304.2, D301.1 (K), L4.1, TP302.1, U5.8 (SW)
S_V3: C95.1, U14.6 (V3)
T_BST: C22.1, U2.17 (BST)
T_C3: C26.1, R17.2
T_COMP: C25.1, R16.1, U2.4 (COMP)
T_CZ: C24.1, R16.2
T_EN: J9921.1, JP1.1 (A), R11.2, R12.1, U2.1 (EN/UVLO)
T_FB: C24.2, C25.2, C26.2, R14.2, R15.1, U2.5 (FB)
T_HO: Q2.4 (G), U2.18 (HO)
T_ILIM: C27.1, R13.1, U2.11 (ILIM)
T_LO: Q3.4 (G), U2.13 (LO)
T_NC9: U2.9 (NC)
T_NC16: U2.16 (NC)
T_PG: TP5.1, U2.10 (PGOOD)
T_RT: R10.1, U2.2 (RT)
T_SS: C23.1, U2.3 (SS/TRK)
T_SW: C22.2, L1.1, Q2.1 (S), Q2.2 (S), Q2.3 (S), Q3.5 (D), R13.2, TP3.1, U2.19 (SW)
T_SYNCOUT: U2.7 (SYNCOUT)
T_VCC: C21.1, U2.14 (VCC)
U1_VCAP: C2.1, U1.1 (VCAP)
USB2_ILIM: R9901.1, U9900.5 (ILIM)
USB2_ILIM_MID: R9901.2, R9902.1
USB2_LIMITED_5V: C9907.1, FB1.1, U9904.6 (OUT)
USB2_MAIN_FAULT_NC: U9904.4 (FAULT_N)
USB2_MAIN_ILIM: R9908.1, U9904.5 (ILIM)
USB2_UNUSED_DM: R9907.1, U9902.4 (2D-)
USB2_UNUSED_DP: R9906.1, U9902.3 (2D+)
USB2_UP_OE_N: R9904.1, U9902.6 (OE_N), U9903.1 (OUT)
USB2_VBUS_SENSE: R9909.2, R9910.1, U9903.4 (IN-)
USB2_VREF: C9909.1, U9903.3 (IN+), U9903.5 (REF)
USB_CC1: J10.A5 (CC1), R60.1
USB_CC2: J10.B5 (CC2), R61.1
USB_CONTROL_5V: C205.1, C206.1, C207.1, C208.1, C9908.1, L3.2, R201.1, R207.1, TP201.1, U9904.1 (IN), U9904.3 (EN)
USB_DM: J10.A7 (D-), J10.B7 (D-), U11.3 (IO2), U11.4 (IO2), U9902.7 (D-)
USB_DP: J10.A6 (D+), J10.B6 (D+), U11.1 (IO1), U11.6 (IO1), U9902.8 (D+)
V3_IO: C66.1, C98.1, C99.1, R76.1, R77.1, U14.5 (VIO), U15.8 (VCC), U16.8 (VCC), U17.5 (VOUT)
V5_USB: C65.1, C72.1, C96.1, C97.1, C7021.1, C9902.1, FB2.1, U12.35 (DVDD), U14.7 (VDD5), U14.8 (VBUS), U17.1 (VIN), U17.3 (EN), U7006.1 (VIN), U7006.3 (EN), U7009.5 (VBUS), U9900.6 (OUT)
V5_USB_HUB: C60.1, C61.1, C62.1, C9900.1, C9901.1, FB1.2, U10.19 (V5), U9900.1 (IN)
VBAT: F1.2, F2.2, J5.2, J5.4
VBAT_L: C1.1, C2.2, D1.1 (A1), F2.1, Q1.1 (S), Q1.2 (S), Q1.3 (S), U1.3 (EN), U1.6 (ANODE)
VBUS_IN: C67.1, J10.A4 (VBUS), J10.A9 (VBUS), J10.B4 (VBUS), J10.B9 (VBUS), R9903.1, R9909.1, U11.5 (VBUS)
VIN: C3.1, C4.1, C5.1, C10.1, C11.1, C12.1, C13.1, C14.1, C15.1, C101.1, C102.1, C103.1, C201.1, C202.1, C203.1, C301.1, C302.1, C303.1, C401.1, C402.1, C403.1, C501.1, C502.1, C503.1, F7000.1, Q1.5 (D), Q2.5 (D), R1.1, R11.1, R104.1, R204.1, R304.1, R404.1, R504.1, TP1.1, U1.4 (CATHODE), U2.20 (VIN), U3.2 (VIN), U4.2 (VIN), U5.2 (VIN), U6.2 (VIN), U7.2 (VIN)
VMOT: F1.1, J2.2

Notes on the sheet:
BASE. A. Battery input, motor pass-through, logic protection
BASE. B. 24V for Thor dev kit (8A connector ceiling; unqualified) (LM5146 sync buck, 200 kHz)
BASE. C. 5V / 5A Raspberry Pi
BASE. D. 5V / 5A OAK-D depth camera
BASE. E. XL330 servo power, 5 V, two daisy-chain sockets
BASE. F. XL430 servo power, 10.8 V, one daisy-chain socket
BASE. G. 11.7V / 5A Audio amplifier
BASE. I. USB in + 4-port hub (CH334F)
BASE. J. USB audio (CM108B) + 2x15W class-D amp (TPA3118D2) on the 12V audio rail
BASE. K. Dynamixel USB interface: CH342F dual serial + half-duplex buffers (U2D2 replacement)
BASE. H. Mounting
BASE. I. USB attachment slew control
IO. A. Dedicated MG90S servo5V (5A target unqualified)
IO. A. Servo5V trim to4.992V nominal
IO. A. Input bulk
IO. A. Local input surge footprint
IO. A. Servo pulse bulk
IO. B2. PWM USB MCU and independent USB logic supply
IO. D. Three5V PWM outputs, default disabled
IO. E. Service
IO. E. Mounting
USB2. USB2 CONTROL. Local supply and host-controlled data attachment
BRANCH. PWM converter input fuse
THOR OUTPUT. Standard four-contact power cable
SERVICE. Optional local regulator OFF shunts
MOUNT. Harness support
ENGINEERING PROTOTYPE; final layout/assembly review and bench qualification required. External mechanical DPST disconnect: STOP ROBOT BEFORE OFF. 27–33V intended battery operation,33.6V full; individual pack-source fuses required. J2 is original fused BATTERY-VOLTAGE motor passthrough to existing F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

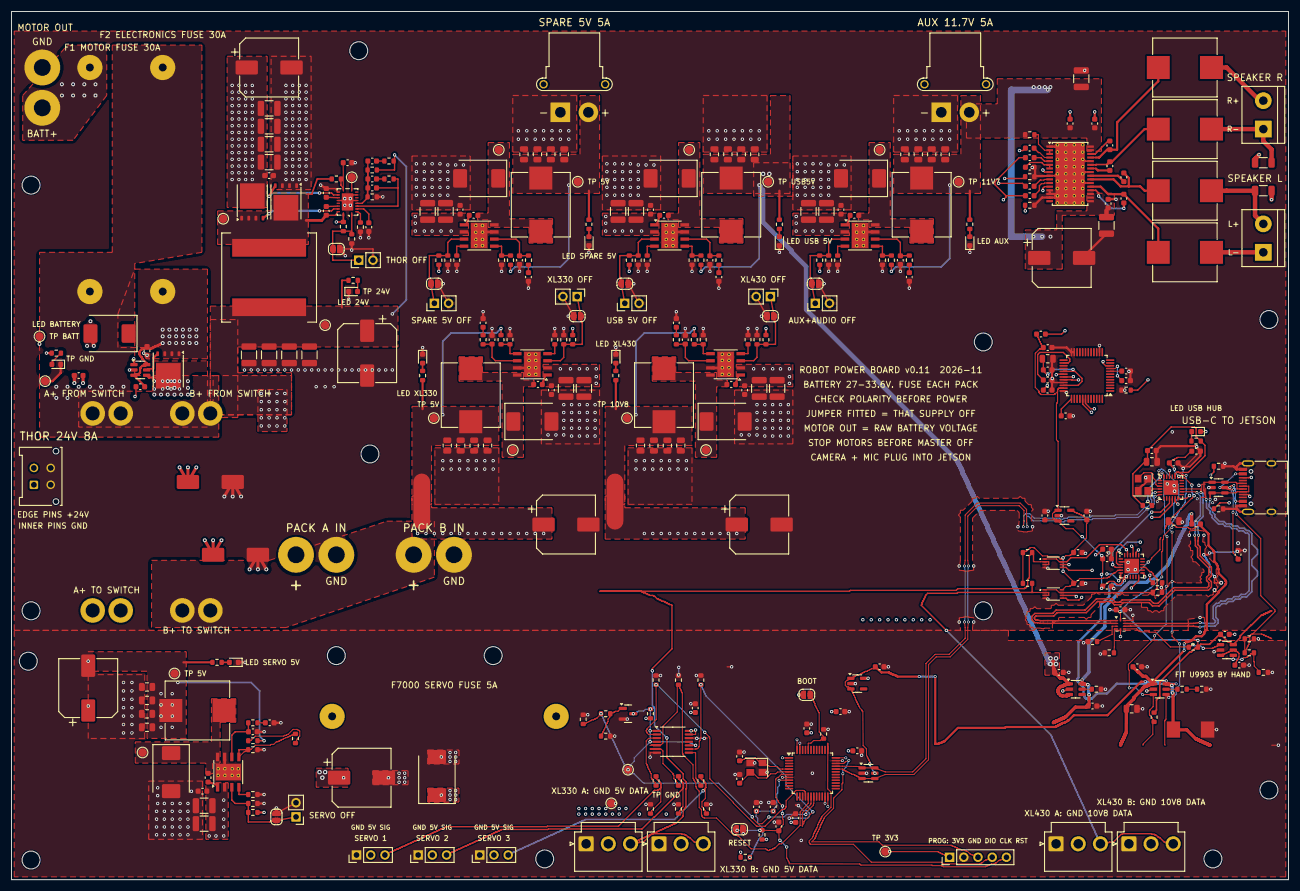
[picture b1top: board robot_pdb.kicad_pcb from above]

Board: 4 copper layers, 228.0 x 155.0 mm, 366 parts (0 on the bottom side), 172 nets.

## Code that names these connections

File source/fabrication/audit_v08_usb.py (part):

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  if all(r['literal_centreline_model'].get(k) is not None for r in (host,hub) for k in ('positive_mm','negative_mm')):
   lp=sum(r['literal_centreline_model']['positive_mm'] for r in (host,hub));ln=sum(r['literal_centreline_model']['negative_mm'] for r in (host,hub));row.update(literal_signed_P_minus_N_mm=lp-ln,literal_skew_125mm_met=abs(lp-ln)<=1.25,literal_complete_150mm_met=max(lp,ln)<=150)
  chain.append(row)
 switch_expected={'1':'HUB_UP_DP','2':'HUB_UP_DM','6':'USB2_UP_OE_N','7':'USB_DM','8':'USB_DP','9':'GND'};switch_contract={pin:dict(expected_net=net,actual_net=a.pad('U9902',pin).GetNetname(),matches=a.pad('U9902',pin).GetNetname()==net) for pin,net in switch_expected.items()}
 detector=a.detector_contract();transfer_fields=a.own_transfer_fields(channels);stitches=a.transition_stitches(channels);spacing=a.spacing();changed=[k for k,v in hashes.items() if digest(ROOT/k)!=v];changed+=['PCB'] if digest(args.board)!=a.hash else []
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 problems=[]
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
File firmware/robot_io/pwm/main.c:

#include "stm32f0xx.h"
#include "tusb.h"
#include "device/dcd.h"
#include "controller.h"
#include <string.h>
#include <errno.h>

static volatile uint32_t milliseconds;
static volatile bool usb_fault;
static volatile bool hardware_armed;
static volatile uint32_t hardware_last_ms;
static pwm_controller control;
static char line[PWM_LINE_MAX];
static size_t used;
static bool overflow;
uint32_t SystemCoreClock=48000000;

static void outputs_off(void){GPIOB->BSRR=GPIO_BSRR_BR_1;TIM3->CCER=0;hardware_armed=false;}
static void fatal(void){outputs_off();for(;;){}}
void SysTick_Handler(void){
    ++milliseconds;
    /* Independent of USB parsing: drop OE even if the foreground is blocked. */
    if(hardware_armed&&(uint32_t)(milliseconds-hardware_last_ms)>=PWM_WATCHDOG_MS){
        outputs_off();usb_fault=true;
    }
}
uint32_t tusb_time_millis_api(void){return milliseconds;}
void USB_IRQHandler(void){tud_int_handler(0);}
void tud_event_hook_cb(uint8_t rhport,uint32_t event,bool in_isr){
    (void)rhport;(void)in_isr;
    if(event==DCD_EVENT_BUS_RESET_START||event==DCD_EVENT_BUS_RESET_END||
       event==DCD_EVENT_UNPLUGGED||event==DCD_EVENT_SUSPEND){outputs_off();usb_fault=true;}
}
static void disconnected(void){
    outputs_off();pwm_connection(&control,false);used=0;overflow=false;
}
void tud_mount_cb(void){disconnected();}
void tud_umount_cb(void){disconnected();}
void tud_suspend_cb(bool remote_wakeup_en){(void)remote_wakeup_en;disconnected();}
void tud_resume_cb(void){disconnected();}
void tud_cdc_line_state_cb(uint8_t itf,bool dtr,bool rts){
    (void)itf;(void)rts;disconnected();
    if(dtr&&!tud_suspended())pwm_connection(&control,true);
}
static void hardware_init(void){
    RCC->AHBENR|=RCC_AHBENR_GPIOAEN|RCC_AHBENR_GPIOBEN|RCC_AHBENR_GPIOFEN;
    GPIOB->BSRR=GPIO_BSRR_BR_1;
    GPIOB->MODER=(GPIOB->MODER&~(3u<<2))|(1u<<2); /* PB1/OE gate default LOW */
    /* Start independent watchdog before waiting for the crystal. PR=16,
     * RLR=249 =>4000 LSI periods:80–133.4ms at DS9826 Table44's30–50kHz
     * LSI range (VDDA3.3V). Still measure the actual reset/enable timing. */
    IWDG->KR=0xcccc; /* Starting watchdog also starts its LSI clock. */
    IWDG->KR=0x5555;IWDG->PR=2;IWDG->RLR=249;
    while(IWDG->SR){} IWDG->KR=0xaaaa;
    FLASH->ACR=FLASH_ACR_PRFTBE|FLASH_ACR_LATENCY;
    RCC->CR|=RCC_CR_HSEON;while(!(RCC->CR&RCC_CR_HSERDY)){}
    RCC->CFGR2=0; /* HSE/PREDIV1 */
    RCC->CFGR=(RCC->CFGR&~(RCC_CFGR_PLLSRC|RCC_CFGR_PLLMUL|RCC_CFGR_HPRE|RCC_CFGR_PPRE))|
        RCC_CFGR_PLLSRC_HSE_PREDIV|RCC_CFGR_PLLMUL6;
    RCC->CR|=RCC_CR_PLLON;while(!(RCC->CR&RCC_CR_PLLRDY)){}
    RCC->CFGR=(RCC->CFGR&~RCC_CFGR_SW)|RCC_CFGR_SW_PLL;
    while((RCC->CFGR&RCC_CFGR_SWS)!=RCC_CFGR_SWS_PLL){}
    RCC->CFGR3|=RCC_CFGR3_USBSW; /* USB=PLL48MHz, not HSI48 */
    RCC->CR|=RCC_CR_CSSON; /* HSE loss => NMI => outputs disabled */
    RCC->APB1ENR|=RCC_APB1ENR_TIM3EN|RCC_APB1ENR_USBEN;
    /* PA6/PA7/PB0 AF1. PA11/12 USB use embedded PHY/pull-up. */
    GPIOA->AFR[0]=(GPIOA->AFR[0]&~((15u<<24)|(15u<<28)))|(1u<<24)|(1u<<28);
    GPIOB->AFR[0]=(GPIOB->AFR[0]&~15u)|1u;
    GPIOA->MODER=(GPIOA->MODER&~((3u<<12)|(3u<<14)))|(2u<<12)|(2u<<14);
    GPIOB->MODER=(GPIOB->MODER&~3u)|2u;
    TIM3->PSC=47;TIM3->ARR=19999;
    TIM3->CCR1=0;TIM3->CCR2=0;TIM3->CCR3=0;
    TIM3->CCMR1=(6u<<4)|TIM_CCMR1_OC1PE|(6u<<12)|TIM_CCMR1_OC2PE;
    TIM3->CCMR2=(6u<<4)|TIM_CCMR2_OC3PE;
    TIM3->CR1=TIM_CR1_ARPE;TIM3->EGR=TIM_EGR_UG;TIM3->CR1|=TIM_CR1_CEN;
    outputs_off();SysTick_Config(48000);
    NVIC_SetPriority(USB_IRQn,1);NVIC_SetPriority(SysTick_IRQn,0);
}
static void apply_outputs(void){
    /* Prevent update between the three writes: preload transfers on the next
     * frame. UDIS holds pending update events until all CCRs are ready. */
    uint32_t irq=__get_PRIMASK();__disable_irq();
    if(usb_fault||!control.armed){outputs_off();}
    else {
        hardware_last_ms=control.last_ms;
        TIM3->CR1|=TIM_CR1_UDIS;
        TIM3->CCR1=control.widths[0];TIM3->CCR2=control.widths[1];TIM3->CCR3=control.widths[2];
        TIM3->CR1&=~TIM_CR1_UDIS;
        if(!TIM3->CCER){
            /* Initial ARM begins a full, deliberate frame with the staged
             * widths; subsequent updates transfer at natural frame boundaries. */
            TIM3->EGR=TIM_EGR_UG;TIM3->SR=0;
            TIM3->CCER=TIM_CCER_CC1E|TIM_CCER_CC2E|TIM_CCER_CC3E;
            GPIOB->BSRR=GPIO_BSRR_BS_1;
            hardware_armed=true;
        }
    }
    __set_PRIMASK(irq);
}
/* This controller has no heap. Refuse accidental libc allocation explicitly. */
void *_sbrk(int increment){(void)increment;errno=ENOMEM;return (void*)-1;}
static void receive(void){
    /* Strict bounded framing, <=64bytes per foreground turn. Overlong line is
     * discarded to newline; it never refreshes watchdog or changes a channel. */
    char reply[96];unsigned budget=64;
    while(budget--&&tud_cdc_available()){
        char c=(char)tud_cdc_read_char();
        if(c=='\r')continue;
        if(c=='\n'){
            line[used]=0;
            if(!overflow&&used){pwm_command(&control,line,milliseconds,reply,sizeof(reply));apply_outputs();
                if(tud_cdc_write_available()>=strlen(reply))tud_cdc_write(reply,strlen(reply));}
            used=0;overflow=false;
        }else if((unsigned char)c<32||(unsigned char)c>126){overflow=true;}
        else if(used<sizeof(line)-1)line[used++]=c;else overflow=true;
    }
    tud_cdc_write_flush();
}
int main(void){
    hardware_init();
    const uint32_t *uid=(const uint32_t*)UID_BASE;
    pwm_init(&control,uid[0]^uid[1]^uid[2]);
    const tusb_rhport_init_t init={.role=TUSB_ROLE_DEVICE,.speed=TUSB_SPEED_FULL};
    if(!tusb_init(0,&init))fatal();
    for(;;){
        tud_task();
        if(usb_fault){
            uint32_t irq=__get_PRIMASK();__disable_irq();
            disconnected();usb_fault=false;__set_PRIMASK(irq);
            /* A new DTR edge or deliberately reopened connection is required. */
        }
        pwm_tick(&control,milliseconds);apply_outputs();receive();
        IWDG->KR=0xaaaa;
    }
}
